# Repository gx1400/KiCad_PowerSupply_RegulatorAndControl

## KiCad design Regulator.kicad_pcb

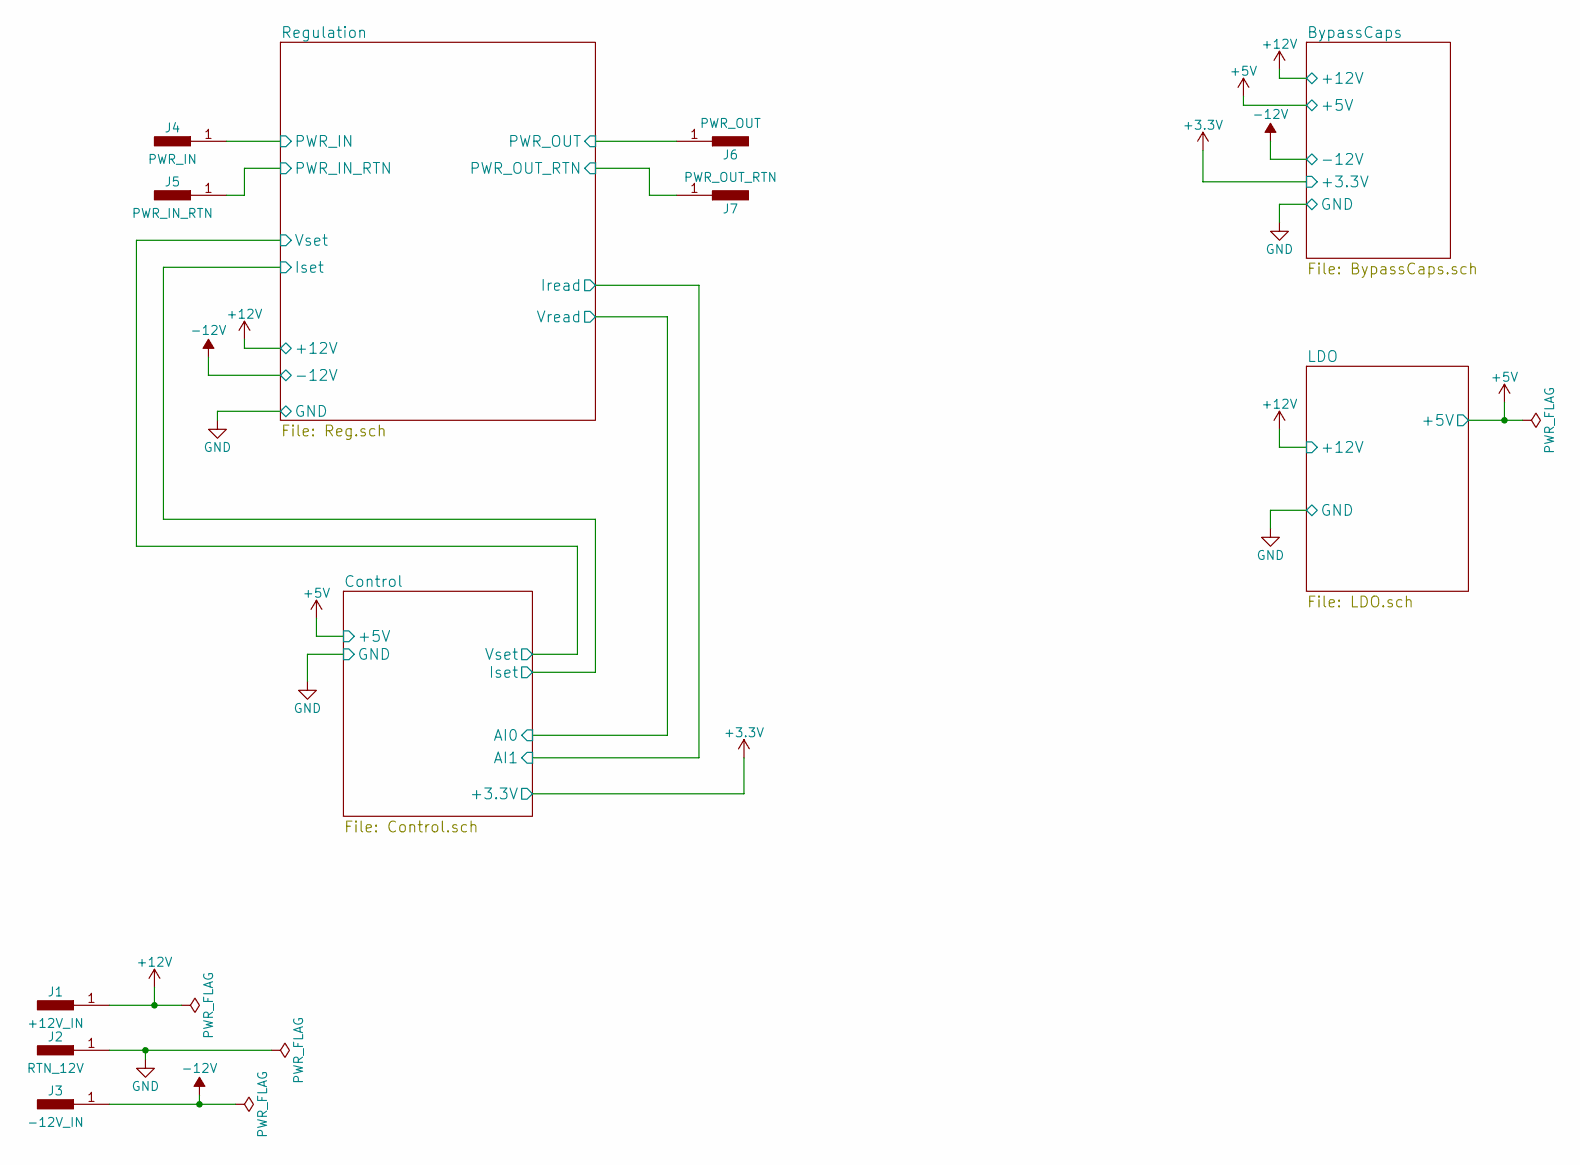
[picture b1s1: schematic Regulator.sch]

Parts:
J1: +12V_IN; SolderWirePad_2x_1-5mmDrill; MPN 1217861-1
J2: RTN_12V; SolderWirePad_2x_1-5mmDrill; MPN 1217861-1
J3: -12V_IN; SolderWirePad_2x_1-5mmDrill; MPN 1217861-1
J4: PWR_IN; SolderWirePad_2x_1-5mmDrill; MPN 1217861-1
J5: PWR_IN_RTN; SolderWirePad_2x_1-5mmDrill; MPN 1217861-1
J6: PWR_OUT; SolderWirePad_2x_1-5mmDrill; MPN 1217861-1
J7: PWR_OUT_RTN; SolderWirePad_2x_1-5mmDrill; MPN 1217861-1

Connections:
+12V: J1.1; also elsewhere on the board
-12V: J3.1; also elsewhere on the board
/Regulation/PWR_IN: J4.1; also elsewhere on the board
/Regulation/PWR_OUT: J6.1; also elsewhere on the board
GND: J2.1, J5.1, J7.1; also elsewhere on the board

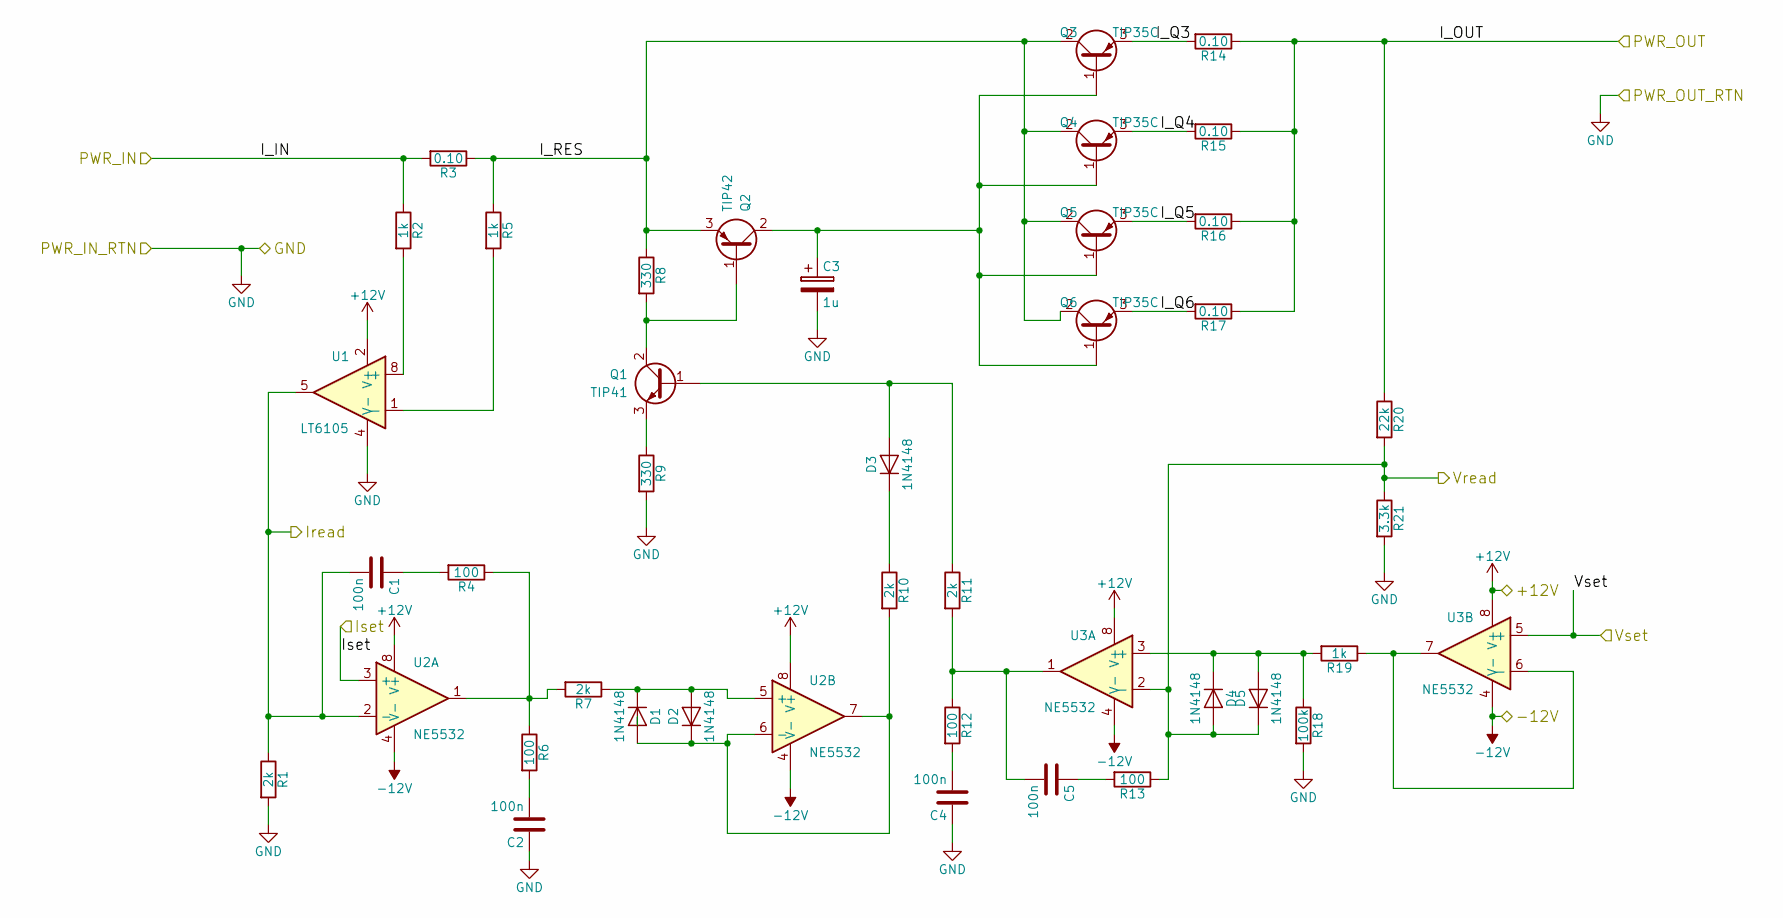
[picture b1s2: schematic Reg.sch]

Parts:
C1, C2, C4, C5: 100n; C_0805_HandSoldering; MPN CL21B104JBCNNNC
C3: 1u; CP_Radial_D4.0mm_P1.50mm; MPN CL21B105KBFNNNG
D1, D2, D3, D4, D5: 1N4148; D_SOD-123; MPN 1N4148W-TP
Q1: TIP41; TO-220_Vertical; MPN TIP41C
Q2: TIP42; TO-220_Vertical; MPN TIP42CTU
Q3, Q4, Q5, Q6: TIP35C; TO-247_TO-3P_Vertical; MPN TIP35CW
R1, R7, R10, R11: 2k; R_0805_HandSoldering; MPN ERJ-6ENF2001V
R2, R5, R19: 1k; R_0805_HandSoldering; MPN ERJ-6GEYJ102V
R3: 0.10; RESISTOR_SMD_BOURNES_DPAK; MPN PWR163S-25-R100F
R4, R6, R12, R13: 100; R_0805_HandSoldering; MPN ERJ-P06J101V
R8, R9: 330; R_0805_HandSoldering; MPN ERJ-6GEYJ331V
R14, R15, R16, R17: 0.10; R_2512_HandSoldering; MPN PE2512FKE070R1L
R18: 100k; R_0805_HandSoldering; MPN ERJ-6ENF1003V
R20: 22k; R_0805_HandSoldering; MPN ERJ-6ENF2202V
R21: 3.3k; R_0805_HandSoldering; MPN ERJ-6ENF3301V
U1: LT6105; MSOP-8_3x3mm_Pitch0.65mm; MPN LT6105CMS8#PBF
U2, U3: NE5532; SOIC-8_3.9x4.9mm_Pitch1.27mm; MPN NE5532DR

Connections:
+12V: U1.2 (V+), U2.8 (V+), U3.8 (V+); also elsewhere on the board
-12V: U2.4 (V-), U3.4 (V-); also elsewhere on the board
/Control/AI0: D4.2 (A), D5.1 (K), R13.1, R20.2, R21.1, U3.2 (-); also elsewhere on the board
/Control/AI1: C1.2, R1.1, U1.5, U2.2 (-); also elsewhere on the board
/Control/Iset: U2.3 (+); also elsewhere on the board
/Control/Vset: U3.5 (+); also elsewhere on the board
/Regulation/I_Q3: Q3.3 (E), R14.2
/Regulation/I_Q4: Q4.3 (E), R15.2
/Regulation/I_Q5: Q5.3 (E), R16.2
/Regulation/I_Q6: Q6.3 (E), R17.2
/Regulation/I_RES: Q2.3 (E), Q3.2 (C), Q4.2 (C), Q5.2 (C), Q6.2 (C), R3.1, R5.1, R8.1
/Regulation/PWR_IN: R2.1, R3.2; also elsewhere on the board
/Regulation/PWR_OUT: R14.1, R15.1, R16.1, R17.1, R20.1; also elsewhere on the board
GND: C2.1, C3.2, C4.1, R1.2, R9.2, R18.2, R21.2, U1.4 (V-); also elsewhere on the board
unnamed: C1.1, R4.2
unnamed: C2.2, R6.2
unnamed: C3.1, Q2.2 (C), Q3.1 (B), Q4.1 (B), Q5.1 (B), Q6.1 (B)
unnamed: C4.2, R12.2
unnamed: C5.1, R13.2
unnamed: C5.2, R11.2, R12.1, U3.1
unnamed: D1.1 (K), D2.2 (A), R7.1, U2.5 (+)
unnamed: D1.2 (A), D2.1 (K), R10.2, U2.6 (-), U2.7
unnamed: D3.1 (K), R10.1
unnamed: D3.2 (A), Q1.1 (B), R11.1
unnamed: D4.1 (K), D5.2 (A), R18.1, R19.2, U3.3 (+)
unnamed: Q1.2 (C), Q2.1 (B), R8.2
unnamed: Q1.3 (E), R9.1
unnamed: R2.2, U1.8 (+)
unnamed: R4.1, R6.1, R7.2, U2.1
unnamed: R5.2, U1.1 (-)
unnamed: R19.1, U3.6 (-), U3.7

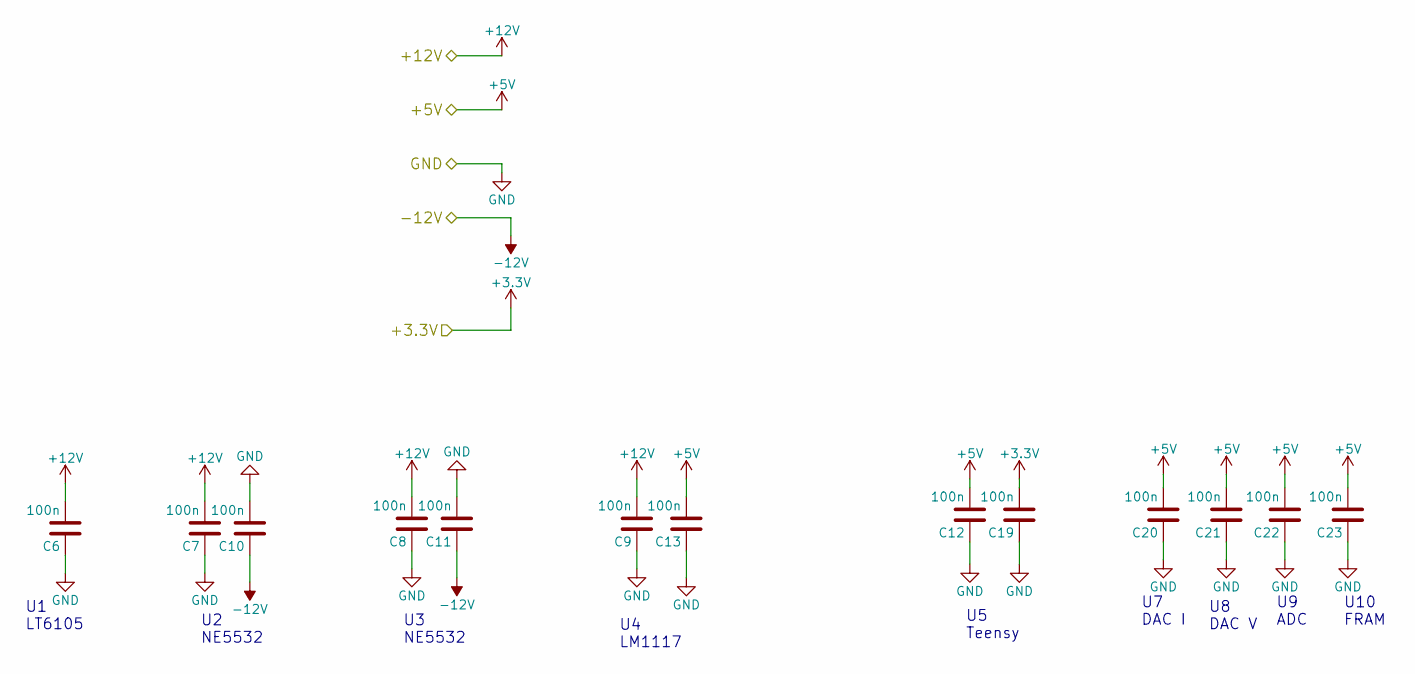
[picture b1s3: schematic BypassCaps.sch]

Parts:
C6, C7, C8, C9, C10, C11, C12, C13, C19, C20, C21, C22, C23: 100n; C_0805_HandSoldering; MPN CL21B104JBCNNNC

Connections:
+3V3: C19.2; also elsewhere on the board
+5V: C12.2, C13.2, C20.2, C21.2, C22.2, C23.2; also elsewhere on the board
+12V: C6.2, C7.2, C8.2, C9.2; also elsewhere on the board
-12V: C10.1, C11.1; also elsewhere on the board
GND: C6.1, C7.1, C8.1, C9.1, C10.2, C11.2, C12.1, C13.1, C19.1, C20.1, C21.1, C22.1, C23.1; also elsewhere on the board

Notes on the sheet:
U1 LT6105
U2 NE5532
U3 NE5532
U4 LM1117
U5 Teensy
U7 DAC I
U8 DAC V
U9 ADC
U10 FRAM

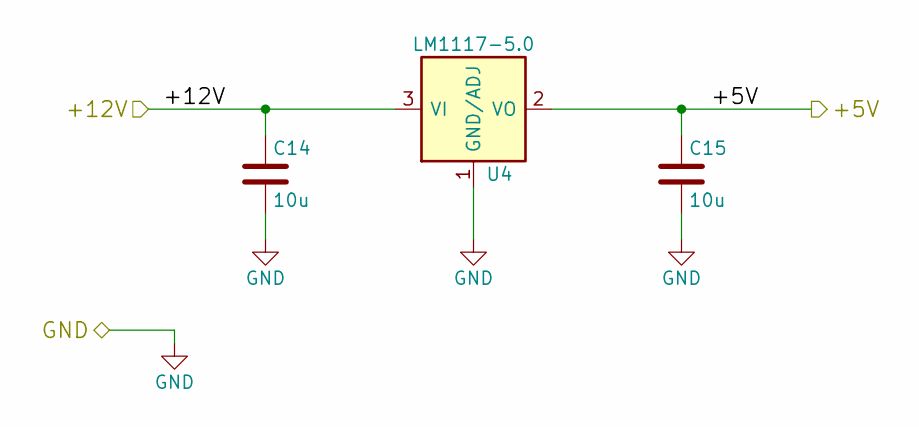
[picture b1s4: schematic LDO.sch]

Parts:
C14, C15: 10u; C_0805_HandSoldering; MPN F951C106MPAAQ2
U4: LM1117-5.0; SOT-223; MPN LM1117MP-5.0/NOPB

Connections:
+5V: C15.1, U4.2 (VO), U4.4 (VO); also elsewhere on the board
+12V: C14.1, U4.3 (VI); also elsewhere on the board
GND: C14.2, C15.2, U4.1 (GND/ADJ); also elsewhere on the board

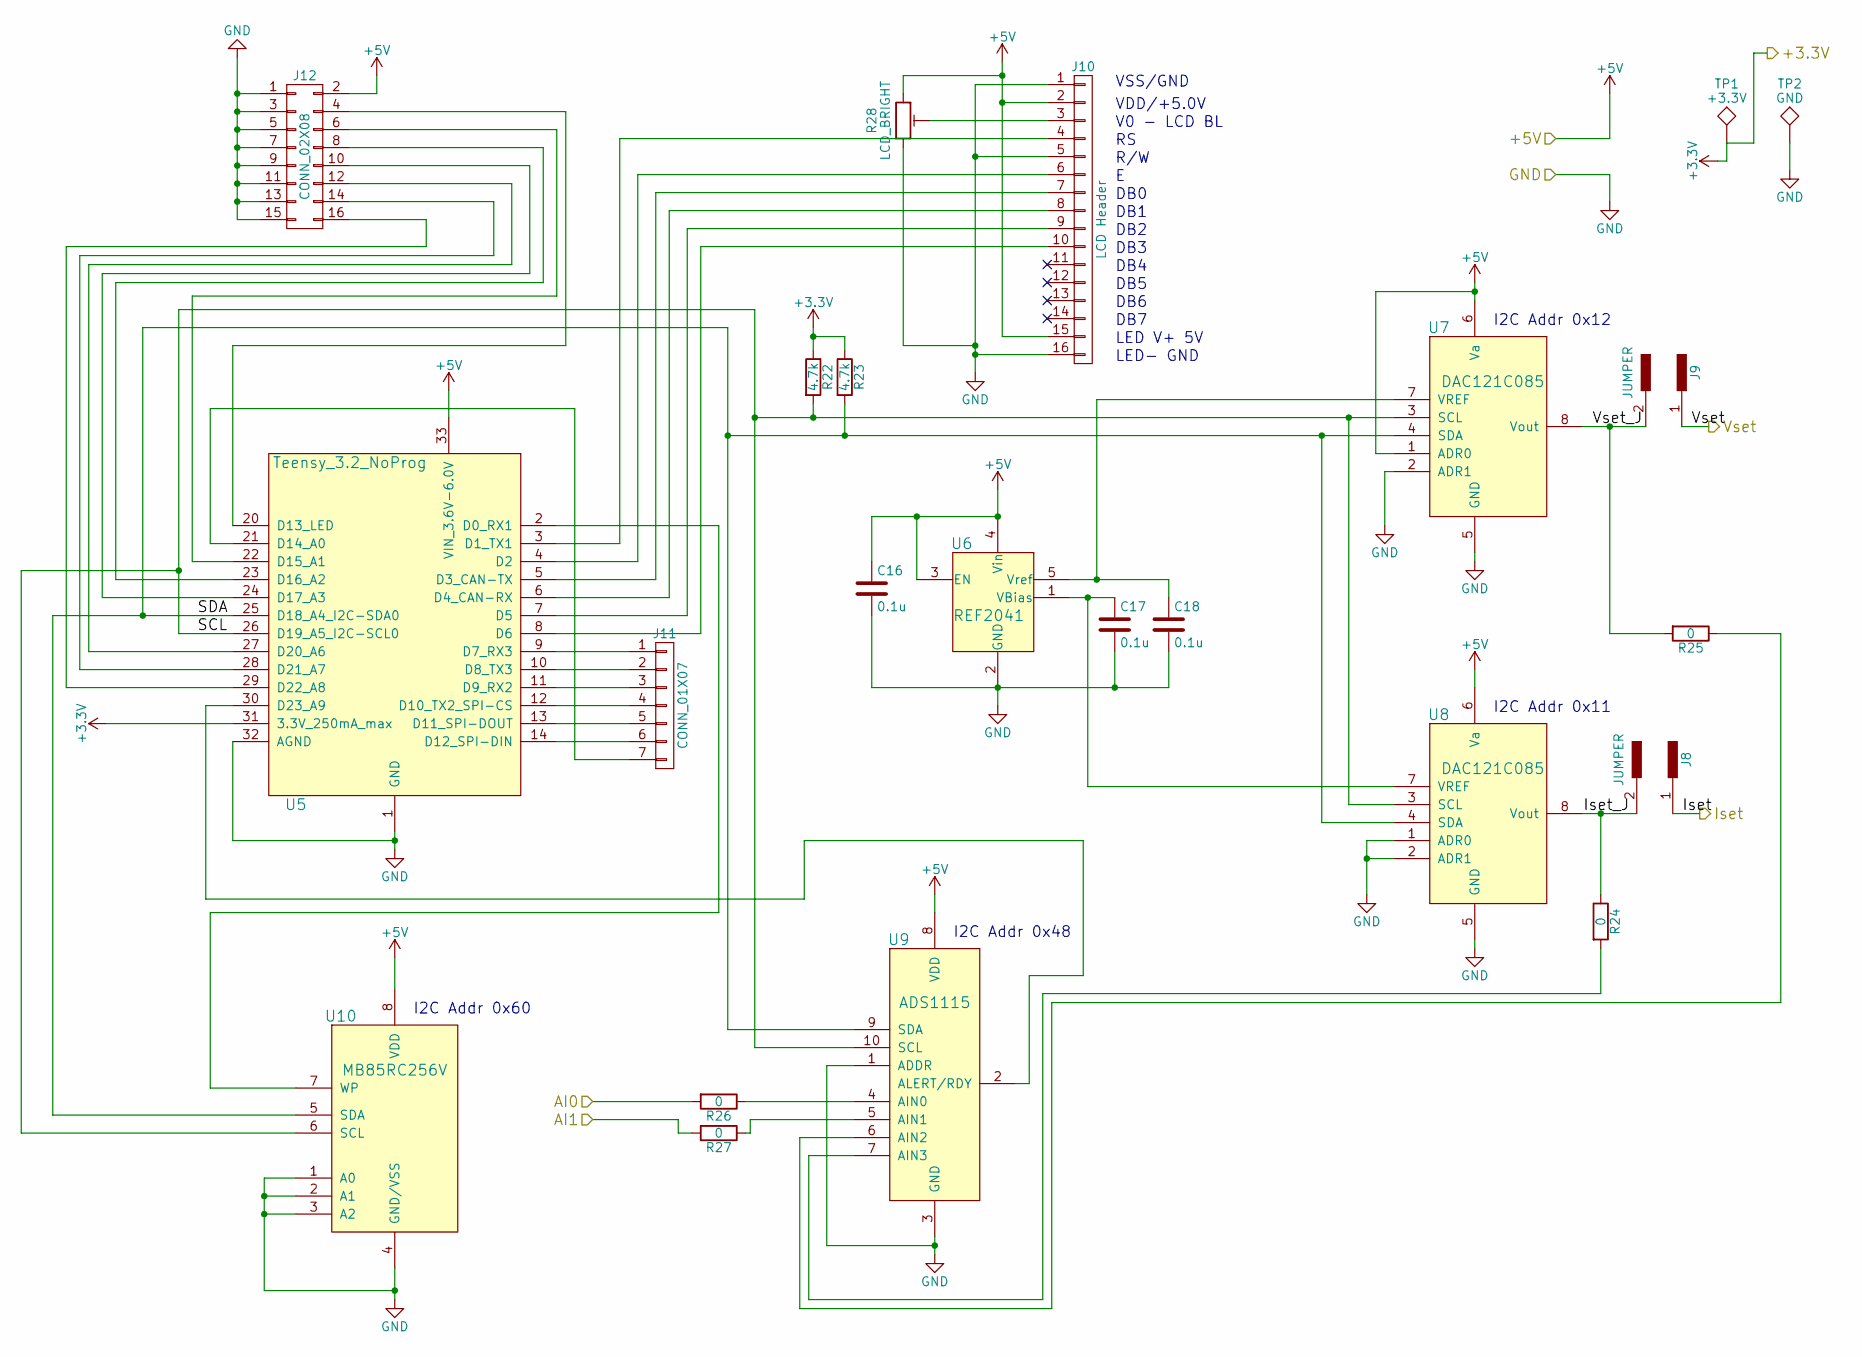
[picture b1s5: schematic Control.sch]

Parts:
C16, C17, C18: 0.1u; C_0805_HandSoldering; MPN C0805C104K4RACTU
J8, J9: JUMPER; R_0805_HandSoldering
J10: LCD Header; Pin_Header_Straight_1x16_Pitch2.54mm
J11: CONN_01X07; Pin_Header_Straight_1x07_Pitch2.54mm
J12: CONN_02X08; IDC_Header_Straight_16pins
R22, R23: 4.7k; R_0805_HandSoldering; MPN ERJ-6GEYJ472V
R24, R25, R26, R27: 0; R_0805_HandSoldering; MPN ERJ-6GEY0R00V
R28: LCD_BRIGHT; Potentiometer_Trimmer_Bourns_3266Y; MPN 3266Y-1-503LF
TP1: +3.3V; Test_Point_Keystone_5000-5004_Miniature; MPN 5000
TP2: GND; Test_Point_Keystone_5000-5004_Miniature; MPN 5001
U5: Teensy_3.2_NoProg; CUSTOM_Teensy_3.2_NoProg; MPN Teensy3.2
U6: REF2041; SOT-23-5_HandSoldering
U7, U8: DAC121C085; MSOP-8_3x3mm_Pitch0.65mm; MPN DAC121C085CIMM/NOPB
U9: ADS1115; MSOP-10_3x3mm_Pitch0.5mm; MPN ADS1115IDGST
U10: MB85RC256V; SOIJ-8_5.3x5.3mm_Pitch1.27mm; MPN MB85RC256VPF-G-JNERE2

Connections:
+3V3: R22.1, R23.1, TP1.1, U5.31 (3.3V_250mA_max); also elsewhere on the board
+5V: C16.1, J10.2, J10.15, J12.2, R28.1, U5.33 (VIN_3.6V-6.0V), U6.3 (EN), U6.4 (Vin), U7.1 (ADR0), U7.6 (Va), U8.6 (Va), U9.8 (VDD), U10.8 (VDD); also elsewhere on the board
/Control/AI0: R26.2; also elsewhere on the board
/Control/AI1: R27.2; also elsewhere on the board
/Control/Iset: J8.1; also elsewhere on the board
/Control/Iset_J: J8.2, R24.1, U8.8 (Vout)
/Control/SCL: R22.2, U5.26 (D19_A5_I2C-SCL0), U7.3 (SCL), U8.3 (SCL), U9.10 (SCL), U10.6 (SCL)
/Control/SDA: R23.2, U5.25 (D18_A4_I2C-SDA0), U7.4 (SDA), U8.4 (SDA), U9.9 (SDA), U10.5 (SDA)
/Control/Vset: J9.1; also elsewhere on the board
/Control/Vset_J: J9.2, R25.2, U7.8 (Vout)
GND: C16.2, C17.2, C18.2, J10.1, J10.5, J10.16, J12.1, J12.3, J12.5, J12.7, J12.9, J12.11, J12.13, J12.15, R28.3, TP2.1, U5.1 (GND), U5.32 (AGND), U6.2 (GND), U7.2 (ADR1), U7.5 (GND), U8.1 (ADR0), U8.2 (ADR1), U8.5 (GND), U9.1 (ADDR), U9.3 (GND), U10.1 (A0), U10.2 (A1), U10.3 (A2), U10.4 (GND/VSS); also elsewhere on the board
unnamed: C17.1, U6.1 (VBias), U8.7 (VREF)
unnamed: C18.1, U6.5 (Vref), U7.7 (VREF)
unnamed: J10.3, R28.2
unnamed: J10.4, U5.3 (D1_TX1)
unnamed: J10.6, U5.4 (D2)
unnamed: J10.7, U5.5 (D3_CAN-TX)
unnamed: J10.8, U5.6 (D4_CAN-RX)
unnamed: J10.9, U5.7 (D5)
unnamed: J10.10, U5.8 (D6)
unnamed: J11.1, U5.9 (D7_RX3)
unnamed: J11.2, U5.10 (D8_TX3)
unnamed: J11.3, U5.11 (D9_RX2)
unnamed: J11.4, U5.12 (D10_TX2_SPI-CS)
unnamed: J11.5, U5.13 (D11_SPI-DOUT)
unnamed: J11.6, U5.14 (D12_SPI-DIN)
unnamed: J11.7, U5.21 (D14_A0)
unnamed: J12.4, U5.20 (D13_LED)
unnamed: J12.6, U5.22 (D15_A1)
unnamed: J12.8, U5.23 (D16_A2)
unnamed: J12.10, U5.24 (D17_A3)
unnamed: J12.12, U5.27 (D20_A6)
unnamed: J12.14, U5.28 (D21_A7)
unnamed: J12.16, U5.29 (D22_A8)
unnamed: R24.2, U9.7 (AIN3)
unnamed: R25.1, U9.6 (AIN2)
unnamed: R26.1, U9.4 (AIN0)
unnamed: R27.1, U9.5 (AIN1)
unnamed: U5.30 (D23_A9), U9.2 (ALERT/RDY)
unnamed: U5.2 (D0_RX1), U10.7 (WP)

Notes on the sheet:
I2C Addr 0x12
I2C Addr 0x11
I2C Addr 0x48
I2C Addr 0x60
VSS/GND
VDD/+5.0V
V0 - LCD BL
R/W
DB0
DB1
DB2
DB3
DB4
DB5
DB6
DB7
LED V+ 5V
LED- GND

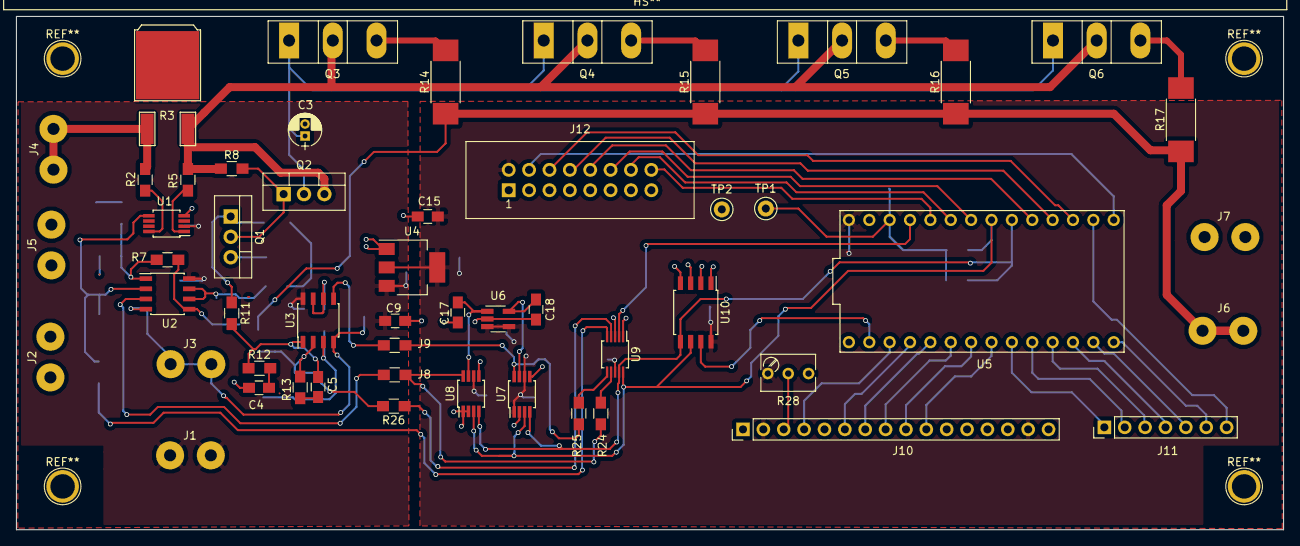
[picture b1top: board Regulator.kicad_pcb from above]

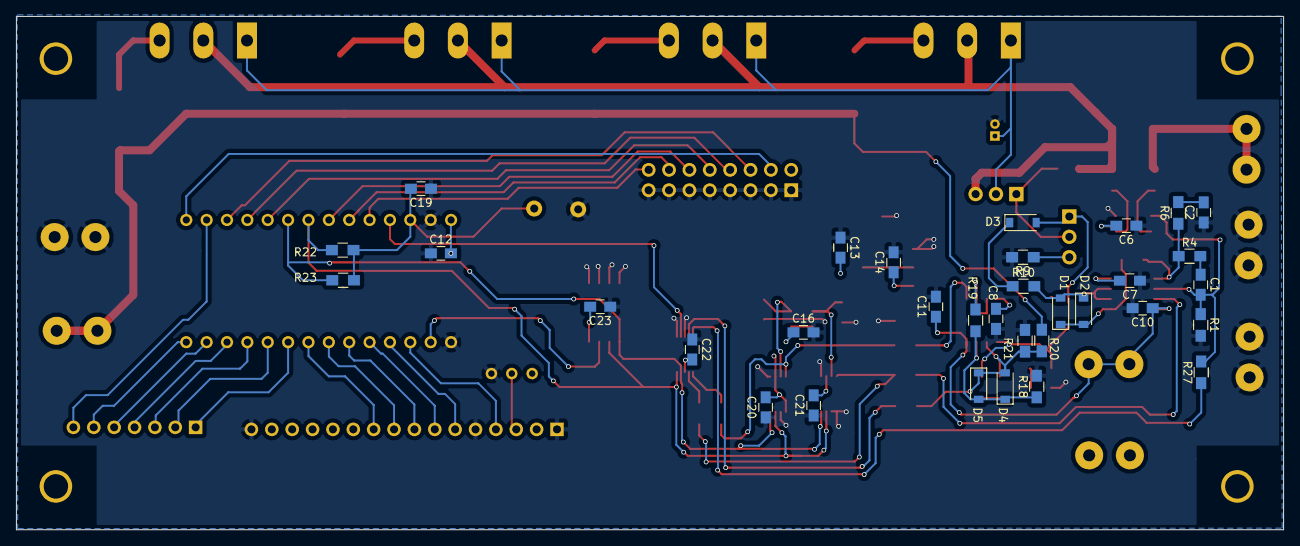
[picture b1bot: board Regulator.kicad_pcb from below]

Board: 2 copper layers, 158.0 x 64.0 mm, 87 parts (33 on the bottom side), 66 nets.

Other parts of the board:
HS**: Heatsink_160x80x26.9mm

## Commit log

2017-05-17 Updates + Lot of routing
2017-05-18 Finished routing
